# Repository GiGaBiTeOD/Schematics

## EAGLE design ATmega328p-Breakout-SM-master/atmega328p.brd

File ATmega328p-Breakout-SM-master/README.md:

# ATmega328p Breakout Board (Surface Mount version)
Eagle board and schematic files for a breakout of the popular ATmega328p microcontroller.

Currently available on Tindie: https://www.tindie.com/products/mwhelectronics/atmega328p-breakout-board/

## License Information
<br />This work is licensed under a <a rel="license" href="http://creativecommons.org/licenses/by-sa/4.0/">Creative Commons Attribution-ShareAlike 4.0 International License</a>.

Distributed as-is; no warranty is given.

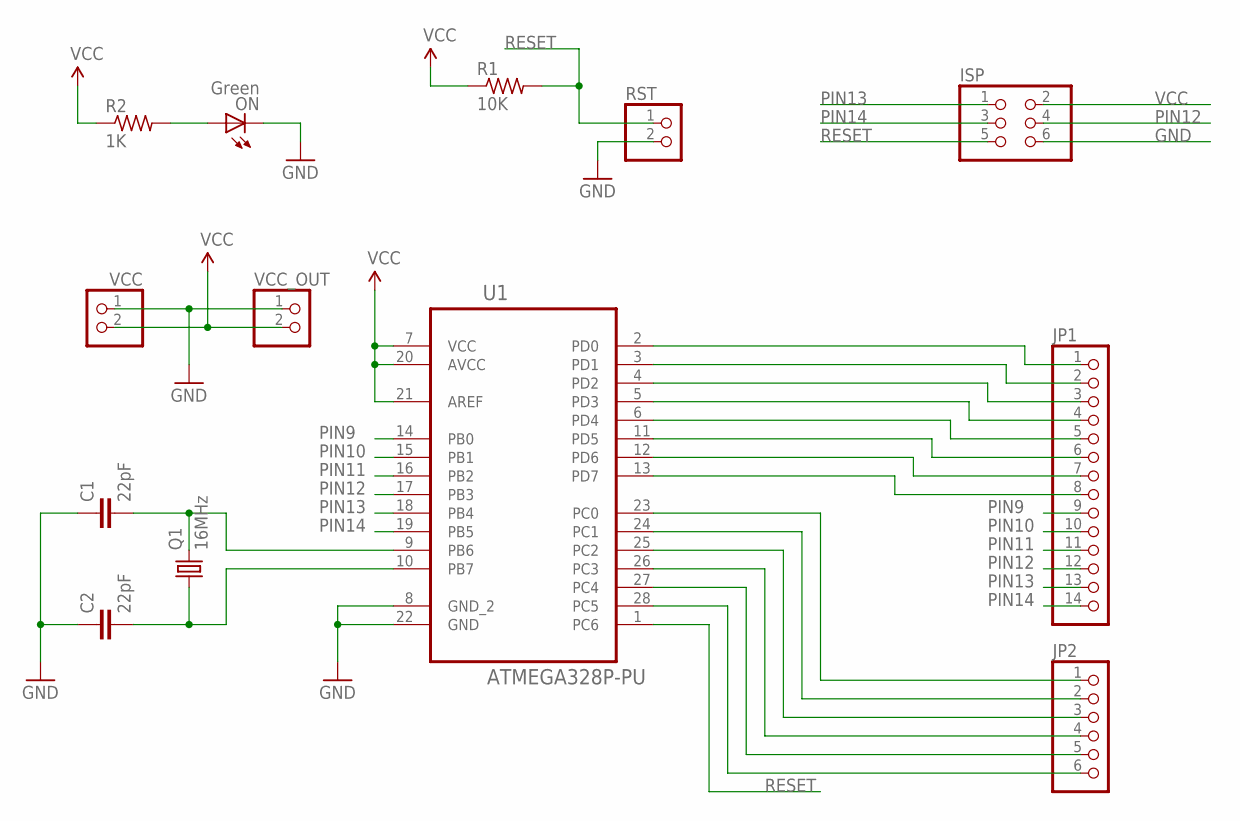
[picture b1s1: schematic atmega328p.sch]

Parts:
C1, C2: 22pF; C0603
ISP: PINHD-2X3; 2X03
JP1: PINHD-1X14; 1X14
JP2: PINHD-1X6; 1X06
ON: Green; CHIPLED_0805
Q1: 16MHz; HC49/S
R1: 10K; R0805
R2: 1K; R0805
RST: PINHD-1X2; 1X02
U1: ATMEGA328P-PU; DIP254P762X457-28
VCC: PINHD-1X2; 1X02
VCC_OUT: PINHD-1X2; 1X02

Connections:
GND: C1.1, C2.1, ISP.6, ON.C, RST.2, U1.8 (GND_2), U1.22 (GND), VCC.1, VCC_OUT.1
unnamed: C1.2, Q1.2, U1.9 (PB6)
unnamed: C2.2, Q1.1, U1.10 (PB7)
unnamed: ON.A, R2.2
unnamed: JP1.1, U1.2 (PD0)
unnamed: JP1.2, U1.3 (PD1)
unnamed: JP1.3, U1.4 (PD2)
unnamed: JP1.4, U1.5 (PD3)
unnamed: JP1.5, U1.6 (PD4)
unnamed: JP1.6, U1.11 (PD5)
unnamed: JP1.7, U1.12 (PD6)
unnamed: JP1.8, U1.13 (PD7)
unnamed: JP2.1, U1.23 (PC0)
unnamed: JP2.2, U1.24 (PC1)
unnamed: JP2.3, U1.25 (PC2)
unnamed: JP2.4, U1.26 (PC3)
unnamed: JP2.5, U1.27 (PC4)
unnamed: JP2.6, U1.28 (PC5)
PIN9: JP1.9, U1.14 (PB0)
PIN10: JP1.10, U1.15 (PB1)
PIN11: JP1.11, U1.16 (PB2)
PIN12: ISP.4, JP1.12, U1.17 (PB3)
PIN13: ISP.1, JP1.13, U1.18 (PB4)
PIN14: ISP.3, JP1.14, U1.19 (PB5)
RESET: ISP.5, R1.2, RST.1, U1.1 (PC6)
VCC: ISP.2, R1.1, R2.1, U1.7 (VCC), U1.20 (AVCC), U1.21 (AREF), VCC.2, VCC_OUT.2

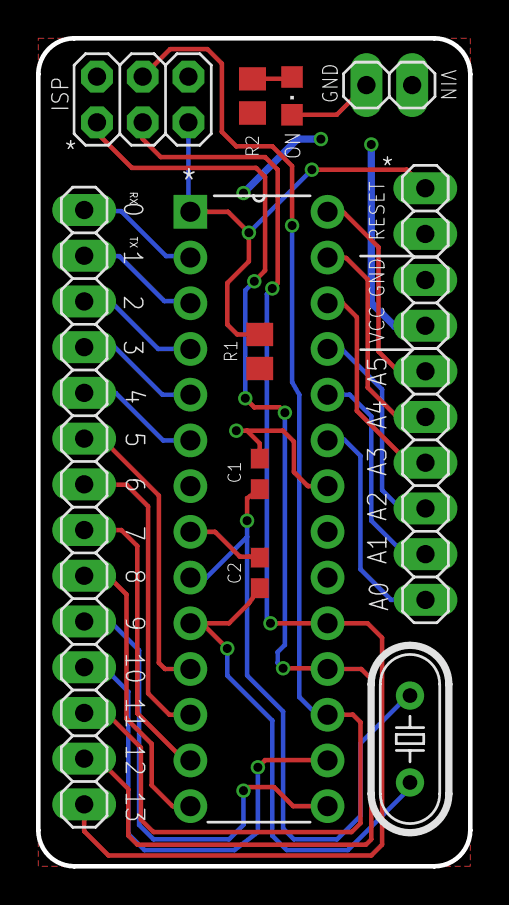
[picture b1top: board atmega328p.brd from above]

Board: 2 copper layers, 24.0 x 46.0 mm, 13 parts (0 on the bottom side), 26 nets.

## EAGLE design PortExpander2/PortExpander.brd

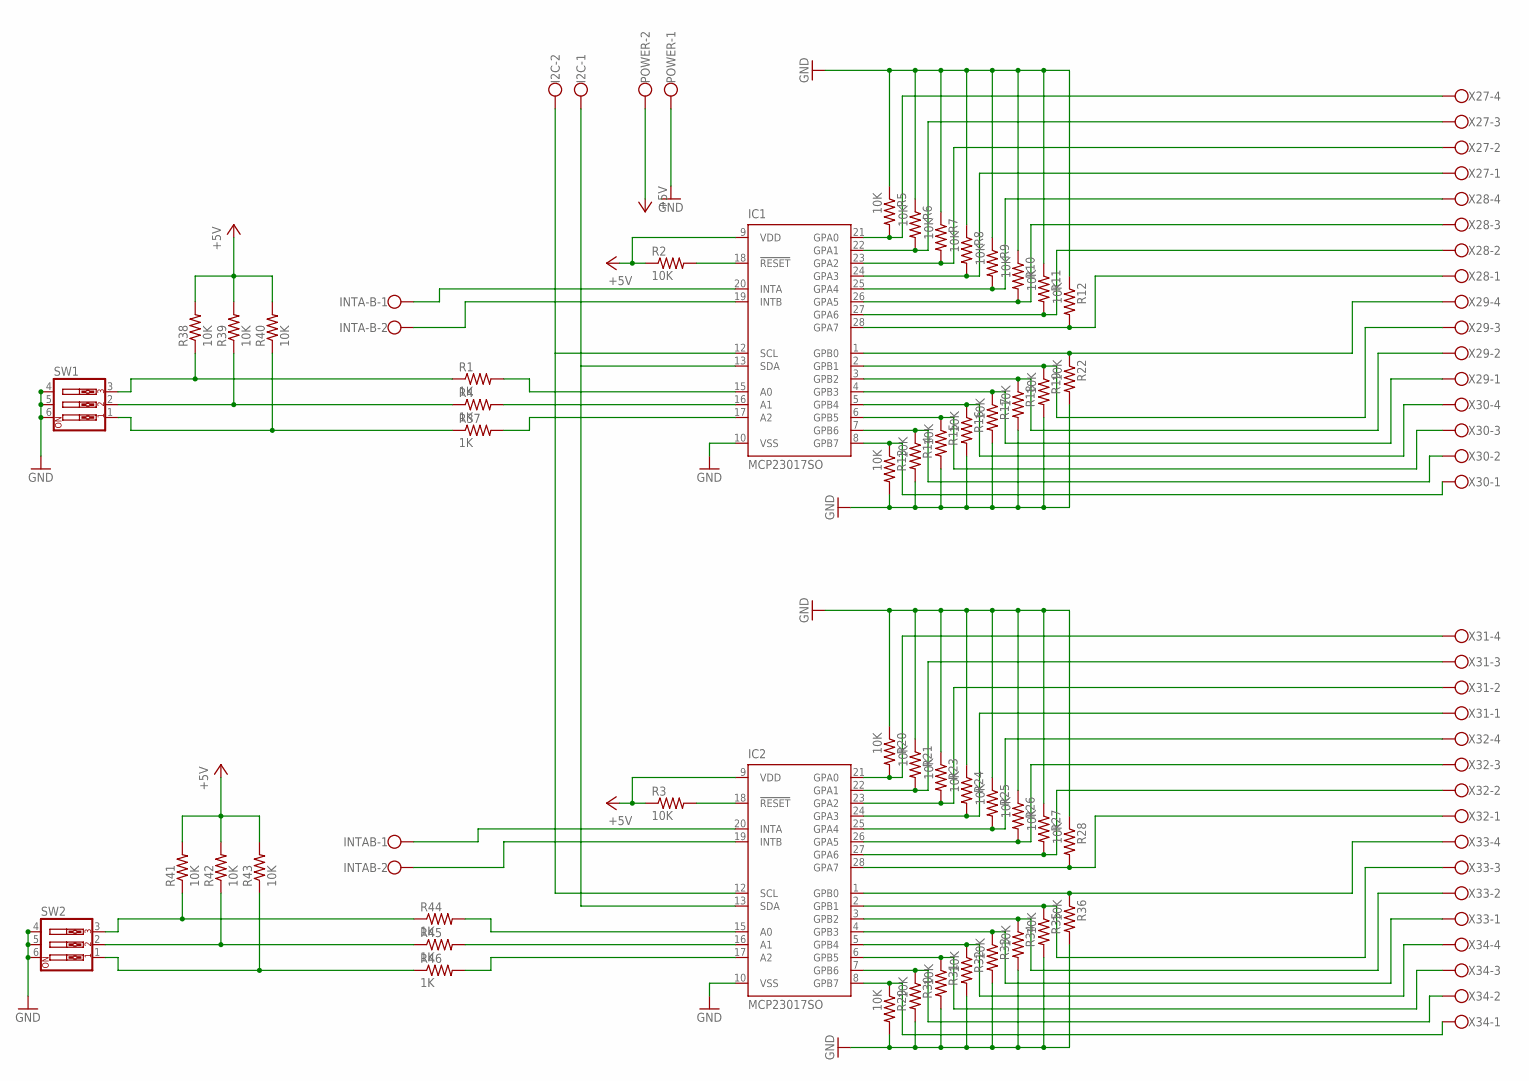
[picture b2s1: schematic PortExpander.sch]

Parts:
I2C: W237-102
IC1, IC2: MCP23017SO; SO28W
INTA-B: W237-102
INTAB: W237-102
POWER: W237-102
R1, R4, R37, R44, R45, R46: 1K; 1206
R2, R3, R5, R6, R7, R8, R9, R10, R11, R12, R13, R14, R15, R16, R17, R18, R19, R20, R21, R22, R23, R24, R25, R26, R27, R28, R29, R30, R31, R32, R33, R34, R35, R36, R38, R39, R40, R41, R42, R43: 10K; 1206
SW1, SW2: SW_DIP-3; EDG-03
X27, X28, X29, X30, X31, X32, X33, X34: W237-4

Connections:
+5V: IC1.9 (VDD), IC2.9 (VDD), POWER.2, R2.1, R3.1, R38.2, R39.2, R40.2, R41.2, R42.2, R43.2
GND: IC1.10 (VSS), IC2.10 (VSS), POWER.1, R5.1, R6.1, R7.1, R8.1, R9.1, R10.1, R11.1, R12.1, R13.2, R14.2, R15.2, R16.2, R17.2, R18.2, R19.2, R20.1, R21.1, R22.2, R23.1, R24.1, R25.1, R26.1, R27.1, R28.1, R29.2, R30.2, R31.2, R32.2, R33.2, R34.2, R35.2, R36.2, SW1.4, SW1.5, SW1.6, SW2.4, SW2.5, SW2.6
GPA0: IC1.21 (GPA0), R5.2, X27.4
GPA0-2: IC2.21 (GPA0), R20.2, X31.4
GPA1: IC1.22 (GPA1), R6.2, X27.3
GPA1-2: IC2.22 (GPA1), R21.2, X31.3
GPA2: IC1.23 (GPA2), R7.2, X27.2
GPA2-2: IC2.23 (GPA2), R23.2, X31.2
GPA3: IC1.24 (GPA3), R8.2, X27.1
GPA3-2: IC2.24 (GPA3), R24.2, X31.1
GPA4: IC1.25 (GPA4), R9.2, X28.4
GPA4-2: IC2.25 (GPA4), R25.2, X32.4
GPA5: IC1.26 (GPA5), R10.2, X28.3
GPA5-2: IC2.26 (GPA5), R26.2, X32.3
GPA6: IC1.27 (GPA6), R11.2, X28.2
GPA6-2: IC2.27 (GPA6), R27.2, X32.2
GPA7: IC1.28 (GPA7), R12.2, X28.1
GPA7-2: IC2.28 (GPA7), R28.2, X32.1
GPB0: IC1.1 (GPB0), R22.1, X29.4
GPB0-2: IC2.1 (GPB0), R36.1, X33.4
GPB1: IC1.2 (GPB1), R19.1, X29.3
GPB1-2: IC2.2 (GPB1), R35.1, X33.3
GPB2: IC1.3 (GPB2), R18.1, X29.2
GPB2-2: IC2.3 (GPB2), R34.1, X33.2
GPB3: IC1.4 (GPB3), R17.1, X29.1
GPB3-2: IC2.4 (GPB3), R33.1, X33.1
GPB4: IC1.5 (GPB4), R16.1, X30.4
GPB4-2: IC2.5 (GPB4), R32.1, X34.4
GPB5: IC1.6 (GPB5), R15.1, X30.3
GPB5-2: IC2.6 (GPB5), R31.1, X34.3
GPB6: IC1.7 (GPB6), R14.1, X30.2
GPB6-2: IC2.7 (GPB6), R30.1, X34.2
GPB7: IC1.8 (GPB7), R13.1, X30.1
GPB7-2: IC2.8 (GPB7), R29.1, X34.1
INTA: IC1.20 (INTA), INTA-B.1
INTA2: IC2.20 (INTA), INTAB.1
INTB: IC1.19 (INTB), INTA-B.2
INTB2: IC2.19 (INTB), INTAB.2
unnamed: IC2.15 (A0), R44.2
unnamed: IC1.15 (A0), R1.2
unnamed: IC1.16 (A1), R4.2
unnamed: IC1.17 (A2), R37.2
unnamed: R1.1, R38.1, SW1.3
unnamed: R4.1, R39.1, SW1.2
unnamed: R37.1, R40.1, SW1.1
unnamed: R41.1, R44.1, SW2.3
unnamed: IC2.16 (A1), R45.2
unnamed: R43.1, R46.1, SW2.1
unnamed: R42.1, R45.1, SW2.2
unnamed: IC2.17 (A2), R46.2
RESET: IC1.18 (!RESET), R2.2
RESET-2: IC2.18 (!RESET), R3.2
SCL: I2C.1, IC1.13 (SDA), IC2.13 (SDA)
SDA: I2C.2, IC1.12 (SCL), IC2.12 (SCL)

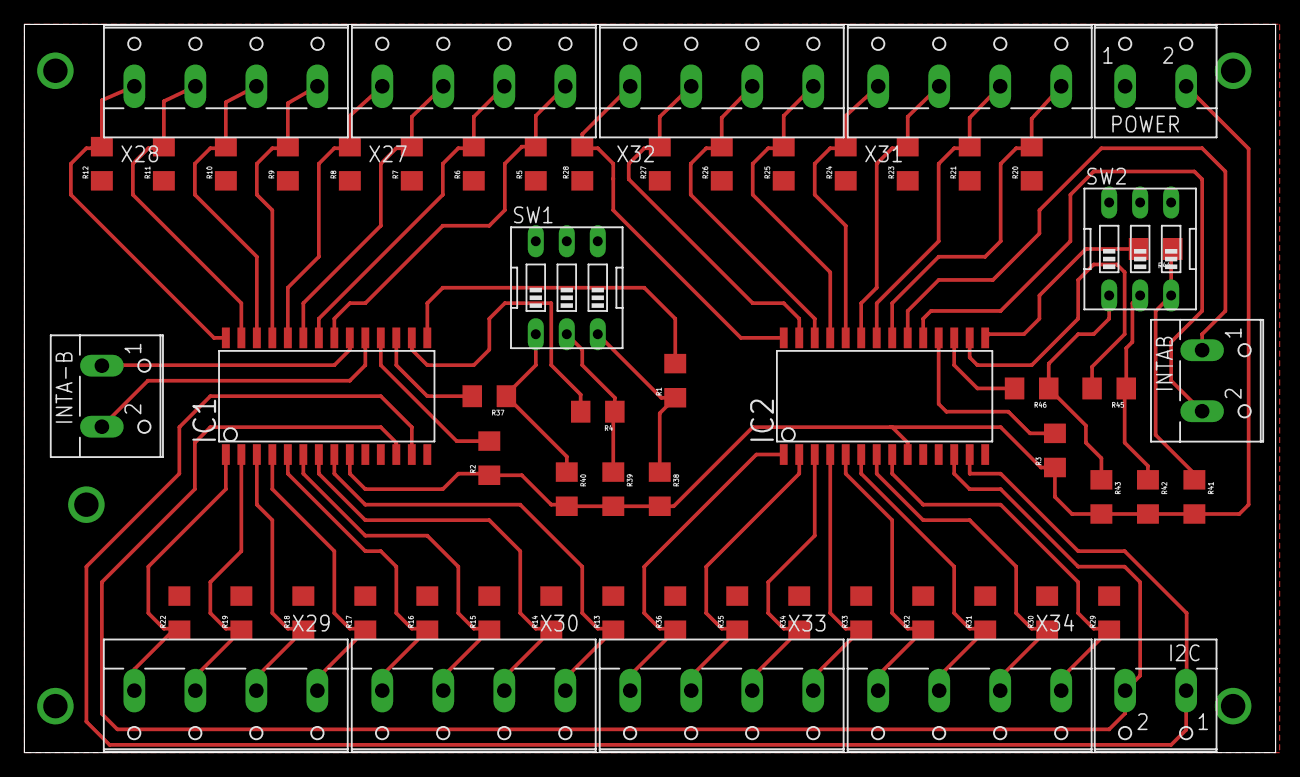
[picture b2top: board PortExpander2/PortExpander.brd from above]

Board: 2 copper layers, 102.5 x 59.7 mm, 62 parts (0 on the bottom side), 54 nets.

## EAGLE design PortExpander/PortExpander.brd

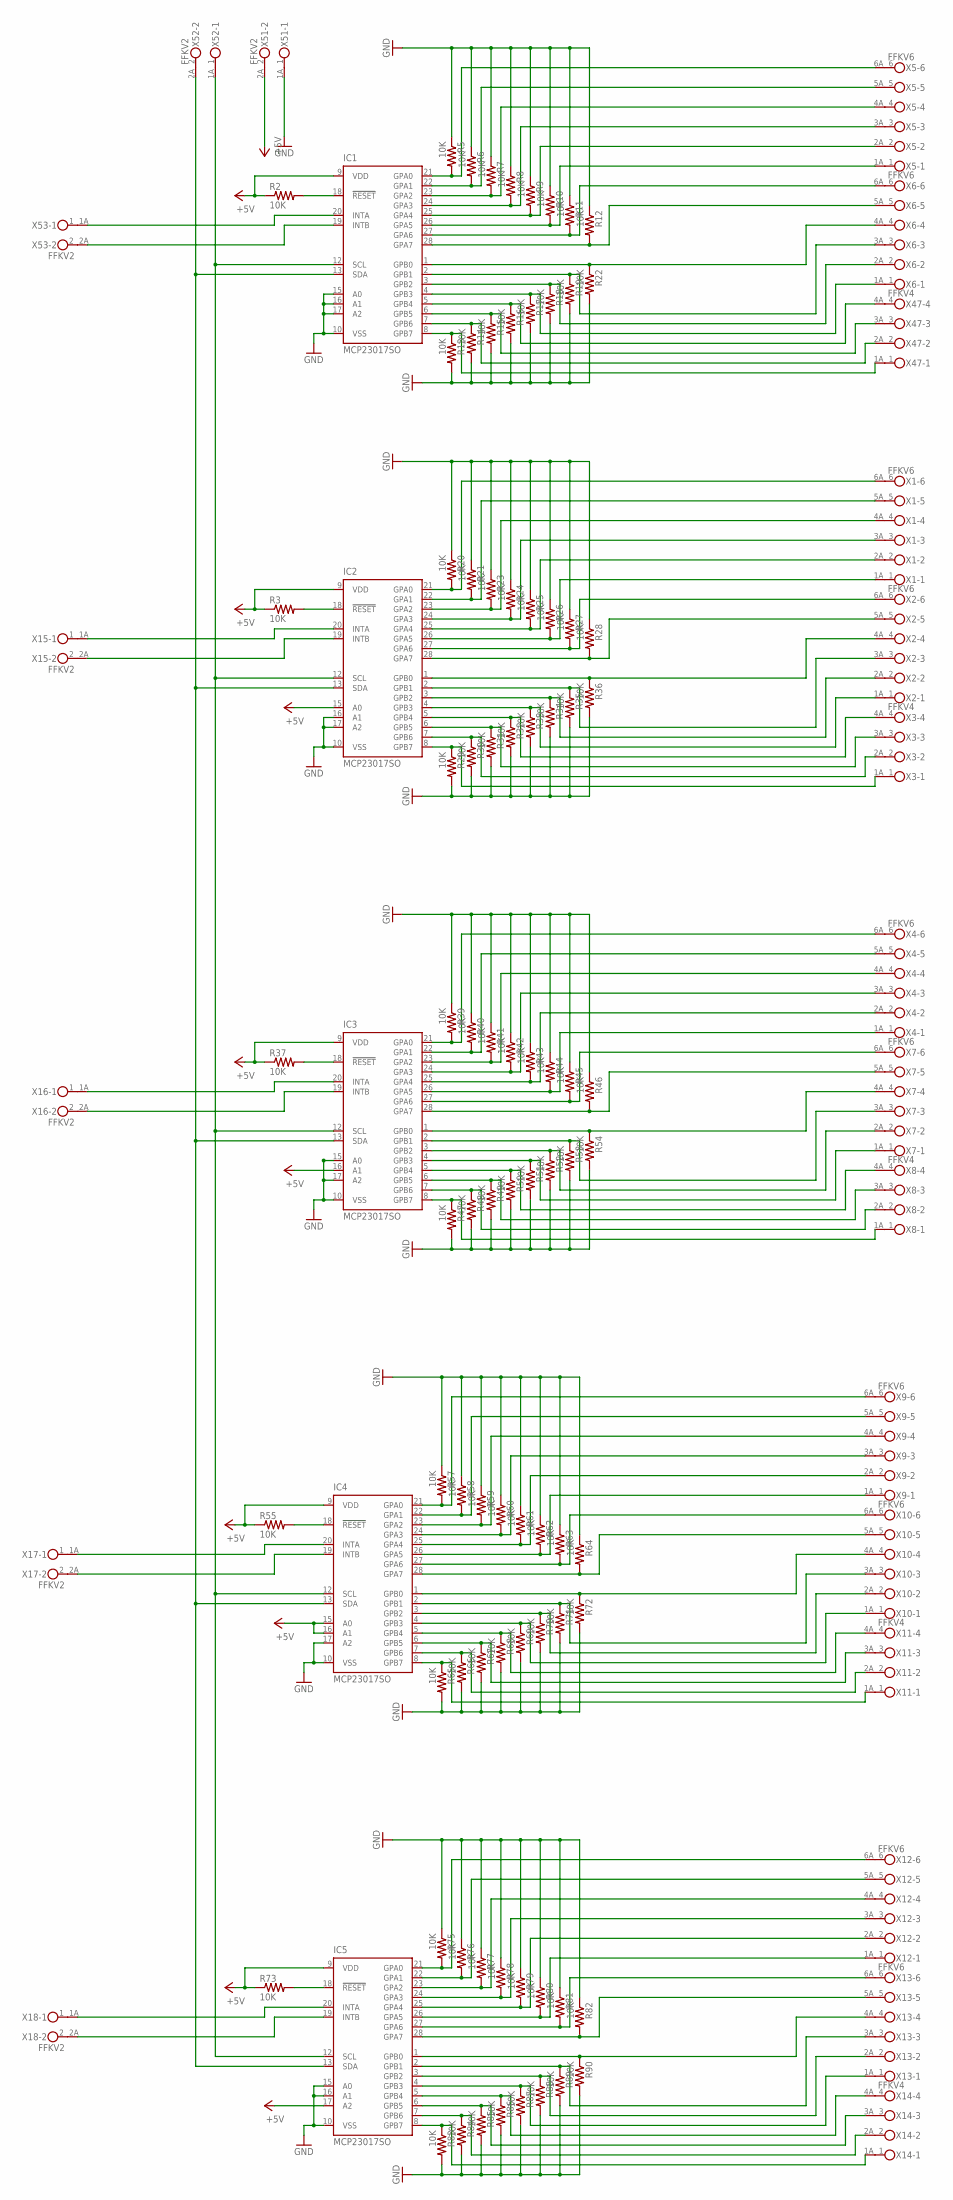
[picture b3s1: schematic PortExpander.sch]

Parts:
IC1, IC2, IC3, IC4, IC5: MCP23017SO; SO28W
R2, R3, R5, R6, R7, R8, R9, R10, R11, R12, R13, R14, R15, R16, R17, R18, R19, R20, R21, R22, R23, R24, R25, R26, R27, R28, R29, R30, R31, R32, R33, R34, R35, R36, R37, R39, R40, R41, R42, R43, R44, R45, R46, R47, R48, R49, R50, R51, R52, R53, R54, R55, R57, R58, R59, R60, R61, R62, R63, R64, R65, R66, R67, R68, R69, R70, R71, R72, R73, R75, R76, R77, R78, R79, R80, R81, R82, R83, R84, R85, R86, R87, R88, R89, R90: 10K; 1206
X1, X2, X4, X5, X6, X7, X9, X10, X12, X13: FFKV6
X3, X8, X11, X14, X47: FFKV4
X15, X16, X17, X18, X51, X52, X53: FFKV2

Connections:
+5V: IC1.9 (VDD), IC2.9 (VDD), IC2.15 (A0), IC3.9 (VDD), IC3.16 (A1), IC4.9 (VDD), IC4.15 (A0), IC4.16 (A1), IC5.9 (VDD), IC5.17 (A2), R2.1, R3.1, R37.1, R55.1, R73.1, X51.2A (2)
GND: IC1.10 (VSS), IC1.15 (A0), IC1.16 (A1), IC1.17 (A2), IC2.10 (VSS), IC2.16 (A1), IC2.17 (A2), IC3.10 (VSS), IC3.15 (A0), IC3.17 (A2), IC4.10 (VSS), IC4.17 (A2), IC5.10 (VSS), IC5.15 (A0), IC5.16 (A1), R5.1, R6.1, R7.1, R8.1, R9.1, R10.1, R11.1, R12.1, R13.2, R14.2, R15.2, R16.2, R17.2, R18.2, R19.2, R20.1, R21.1, R22.2, R23.1, R24.1, R25.1, R26.1, R27.1, R28.1, R29.2, R30.2, R31.2, R32.2, R33.2, R34.2, R35.2, R36.2, R39.1, R40.1, R41.1, R42.1, R43.1, R44.1, R45.1, R46.1, R47.2, R48.2, R49.2, R50.2, R51.2, R52.2, R53.2, R54.2, R57.1, R58.1, R59.1, R60.1, R61.1, R62.1, R63.1, R64.1, R65.2, R66.2, R67.2, R68.2, R69.2, R70.2, R71.2, R72.2, R75.1, R76.1, R77.1, R78.1, R79.1, R80.1, R81.1, R82.1, R83.2, R84.2, R85.2, R86.2, R87.2, R88.2, R89.2, R90.2, X51.1A (2)
unnamed: IC1.18 (!RESET), R2.2
unnamed: IC2.18 (!RESET), R3.2
unnamed: IC1.21 (GPA0), R5.2, X5.6A (2)
unnamed: IC1.22 (GPA1), R6.2, X5.5A (2)
unnamed: IC1.23 (GPA2), R7.2, X5.4A (2)
unnamed: IC1.24 (GPA3), R8.2, X5.3A (2)
unnamed: IC1.25 (GPA4), R9.2, X5.2A (2)
unnamed: IC1.26 (GPA5), R10.2, X5.1A (2)
unnamed: IC1.27 (GPA6), R11.2, X6.6A (2)
unnamed: IC1.28 (GPA7), R12.2, X6.5A (2)
unnamed: IC2.20 (INTA), X15.1A (2)
unnamed: IC1.8 (GPB7), R13.1, X47.1A (2)
unnamed: IC1.7 (GPB6), R14.1, X47.2A (2)
unnamed: IC1.6 (GPB5), R15.1, X47.3A (2)
unnamed: IC1.5 (GPB4), R16.1, X47.4A (2)
unnamed: IC1.4 (GPB3), R17.1, X6.1A (2)
unnamed: IC1.3 (GPB2), R18.1, X6.2A (2)
unnamed: IC1.2 (GPB1), R19.1, X6.3A (2)
unnamed: IC1.1 (GPB0), R22.1, X6.4A (2)
unnamed: IC2.19 (INTB), X15.2A (2)
unnamed: IC2.21 (GPA0), R20.2, X1.6A (2)
unnamed: IC2.22 (GPA1), R21.2, X1.5A (2)
unnamed: IC2.23 (GPA2), R23.2, X1.4A (2)
unnamed: IC2.24 (GPA3), R24.2, X1.3A (2)
unnamed: IC2.25 (GPA4), R25.2, X1.2A (2)
unnamed: IC2.26 (GPA5), R26.2, X1.1A (2)
unnamed: IC2.27 (GPA6), R27.2, X2.6A (2)
unnamed: IC2.28 (GPA7), R28.2, X2.5A (2)
unnamed: IC2.8 (GPB7), R29.1, X3.1A (2)
unnamed: IC2.7 (GPB6), R30.1, X3.2A (2)
unnamed: IC2.6 (GPB5), R31.1, X3.3A (2)
unnamed: IC2.5 (GPB4), R32.1, X3.4A (2)
unnamed: IC2.4 (GPB3), R33.1, X2.1A (2)
unnamed: IC2.3 (GPB2), R34.1, X2.2A (2)
unnamed: IC2.2 (GPB1), R35.1, X2.3A (2)
unnamed: IC2.1 (GPB0), R36.1, X2.4A (2)
unnamed: IC3.18 (!RESET), R37.2
unnamed: IC3.20 (INTA), X16.1A (2)
unnamed: IC3.19 (INTB), X16.2A (2)
unnamed: IC3.21 (GPA0), R39.2, X4.6A (2)
unnamed: IC3.22 (GPA1), R40.2, X4.5A (2)
unnamed: IC3.23 (GPA2), R41.2, X4.4A (2)
unnamed: IC3.24 (GPA3), R42.2, X4.3A (2)
unnamed: IC3.25 (GPA4), R43.2, X4.2A (2)
unnamed: IC3.26 (GPA5), R44.2, X4.1A (2)
unnamed: IC3.27 (GPA6), R45.2, X7.6A (2)
unnamed: IC3.28 (GPA7), R46.2, X7.5A (2)
unnamed: IC3.8 (GPB7), R47.1, X8.1A (2)
unnamed: IC3.7 (GPB6), R48.1, X8.2A (2)
unnamed: IC3.6 (GPB5), R49.1, X8.3A (2)
unnamed: IC3.5 (GPB4), R50.1, X8.4A (2)
unnamed: IC3.4 (GPB3), R51.1, X7.1A (2)
unnamed: IC3.3 (GPB2), R52.1, X7.2A (2)
unnamed: IC3.2 (GPB1), R53.1, X7.3A (2)
unnamed: IC3.1 (GPB0), R54.1, X7.4A (2)
unnamed: IC4.18 (!RESET), R55.2
unnamed: IC4.20 (INTA), X17.1A (2)
unnamed: IC4.19 (INTB), X17.2A (2)
unnamed: IC4.21 (GPA0), R57.2, X9.6A (2)
unnamed: IC4.22 (GPA1), R58.2, X9.5A (2)
unnamed: IC4.23 (GPA2), R59.2, X9.4A (2)
unnamed: IC4.24 (GPA3), R60.2, X9.3A (2)
unnamed: IC1.20 (INTA), X53.1A (2)
unnamed: IC1.19 (INTB), X53.2A (2)
unnamed: IC4.25 (GPA4), R61.2, X9.2A (2)
unnamed: IC4.26 (GPA5), R62.2, X9.1A (2)
unnamed: IC4.27 (GPA6), R63.2, X10.6A (2)
unnamed: IC4.28 (GPA7), R64.2, X10.5A (2)
unnamed: IC4.8 (GPB7), R65.1, X11.1A (2)
unnamed: IC4.7 (GPB6), R66.1, X11.2A (2)
unnamed: IC4.6 (GPB5), R67.1, X11.3A (2)
unnamed: IC4.5 (GPB4), R68.1, X11.4A (2)
unnamed: IC4.4 (GPB3), R69.1, X10.1A (2)
unnamed: IC4.3 (GPB2), R70.1, X10.2A (2)
unnamed: IC4.2 (GPB1), R71.1, X10.3A (2)
unnamed: IC4.1 (GPB0), R72.1, X10.4A (2)
unnamed: IC5.18 (!RESET), R73.2
unnamed: IC5.20 (INTA), X18.1A (2)
unnamed: IC5.19 (INTB), X18.2A (2)
unnamed: IC5.21 (GPA0), R75.2, X12.6A (2)
unnamed: IC5.22 (GPA1), R76.2, X12.5A (2)
unnamed: IC5.23 (GPA2), R77.2, X12.4A (2)
unnamed: IC5.24 (GPA3), R78.2, X12.3A (2)
unnamed: IC5.25 (GPA4), R79.2, X12.2A (2)
unnamed: IC5.26 (GPA5), R80.2, X12.1A (2)
unnamed: IC5.27 (GPA6), R81.2, X13.6A (2)
unnamed: IC5.28 (GPA7), R82.2, X13.5A (2)
unnamed: IC5.8 (GPB7), R83.1, X14.1A (2)
unnamed: IC5.7 (GPB6), R84.1, X14.2A (2)
unnamed: IC5.6 (GPB5), R85.1, X14.3A (2)
unnamed: IC5.5 (GPB4), R86.1, X14.4A (2)
unnamed: IC5.4 (GPB3), R87.1, X13.1A (2)
unnamed: IC5.3 (GPB2), R88.1, X13.2A (2)
unnamed: IC5.2 (GPB1), R89.1, X13.3A (2)
unnamed: IC5.1 (GPB0), R90.1, X13.4A (2)
SCL: IC1.12 (SCL), IC2.12 (SCL), IC3.12 (SCL), IC4.12 (SCL), IC5.12 (SCL), X52.1A (2)
SDA: IC1.13 (SDA), IC2.13 (SDA), IC3.13 (SDA), IC4.13 (SDA), IC5.13 (SDA), X52.2A (2)

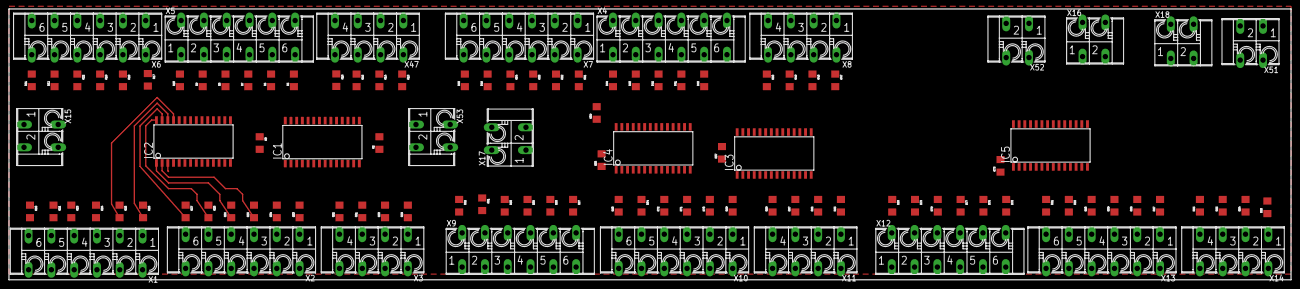
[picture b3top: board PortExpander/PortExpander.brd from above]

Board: 2 copper layers, 285.7 x 60.4 mm, 112 parts (0 on the bottom side), 99 nets.

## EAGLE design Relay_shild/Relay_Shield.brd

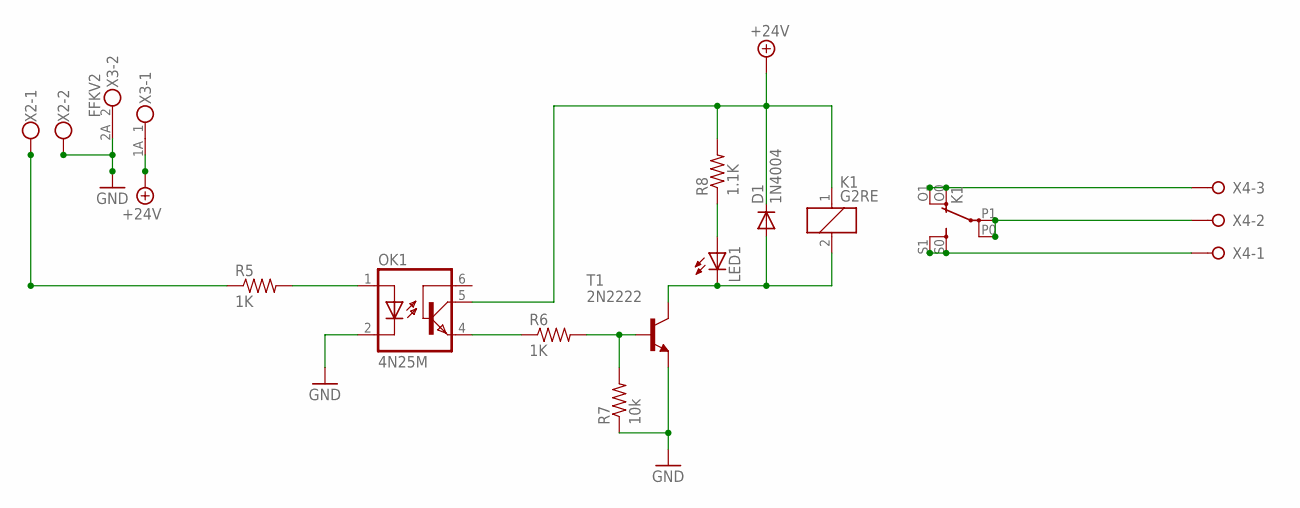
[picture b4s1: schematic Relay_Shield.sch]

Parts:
D1: 1N4004; DO41-10
K1: G2RE
LED1: LED3MM
OK1: 4N25M; DIL06
R5, R6: 1K; 1206
R7: 10k; 1206
R8: 1.1K; 1206
T1: 2N2222; TO18
X2: W237-102
X3: FFKV2
X4: W237-3E

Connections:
+24V: D1.C, K1.1, OK1.5 (COL), R8.2, X3.1A (2)
GND: OK1.2 (C), R7.1, T1.1 (E), X2.2, X3.2A (2)
unnamed: OK1.1 (A), R5.2
unnamed: OK1.4 (EMI), R6.1
unnamed: R6.2, R7.2, T1.2 (B)
unnamed: R5.1, X2.1
unnamed: D1.A, K1.2, LED1.K (C), T1.3 (C)
unnamed: LED1.A, R8.1
unnamed: K1.P0, K1.P1, X4.2
unnamed: K1.O0 (O), K1.O1 (O), X4.3
unnamed: K1.S0 (S), K1.S1 (S), X4.1

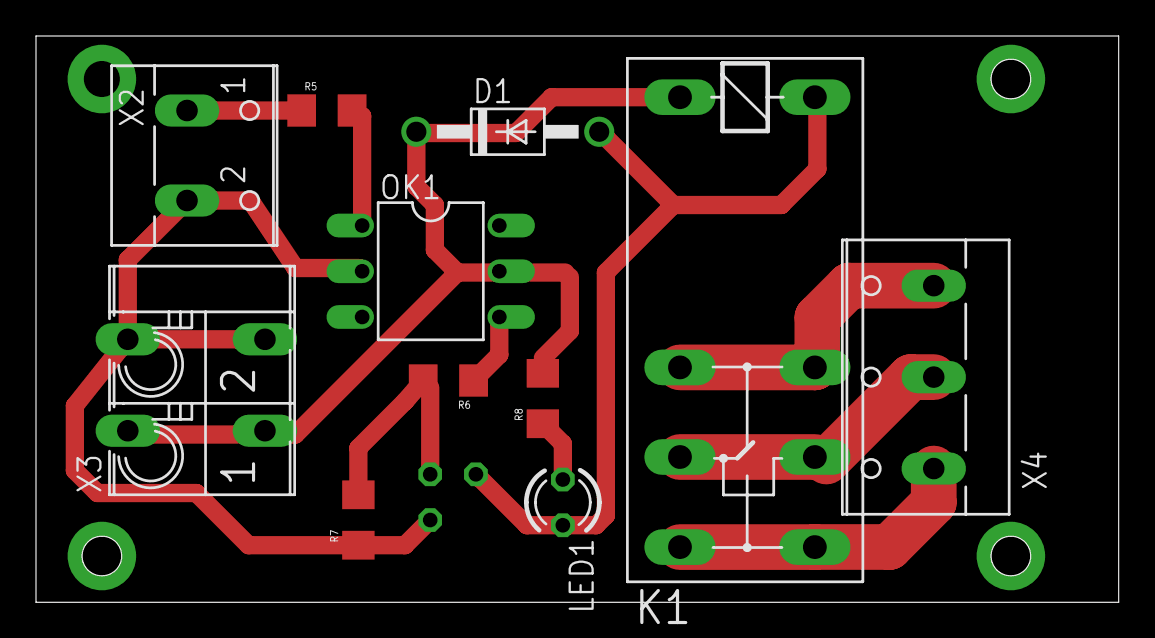
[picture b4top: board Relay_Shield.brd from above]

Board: 2 copper layers, 60.1 x 31.5 mm, 12 parts (1 on the bottom side), 11 nets.

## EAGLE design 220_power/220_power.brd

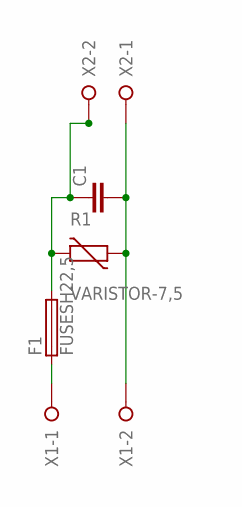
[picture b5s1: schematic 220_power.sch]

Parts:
C1: C15/8; C15B8
F1: FUSESH22,5; SH22,5
R1: VARISTOR-7,5; R-7,5
X1, X2: W237-02P; W237-132

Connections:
unnamed: F1.1, X1.1
unnamed: C1.1, F1.2, R1.2, X2.2
unnamed: C1.2, R1.1, X1.2, X2.1

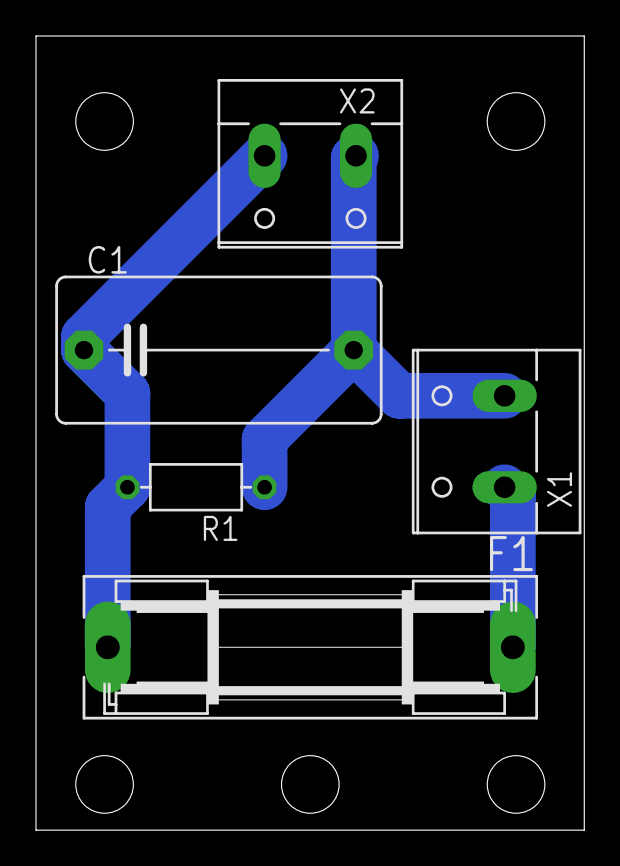
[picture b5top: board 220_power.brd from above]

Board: 2 copper layers, 30.5 x 44.1 mm, 5 parts (0 on the bottom side), 3 nets.

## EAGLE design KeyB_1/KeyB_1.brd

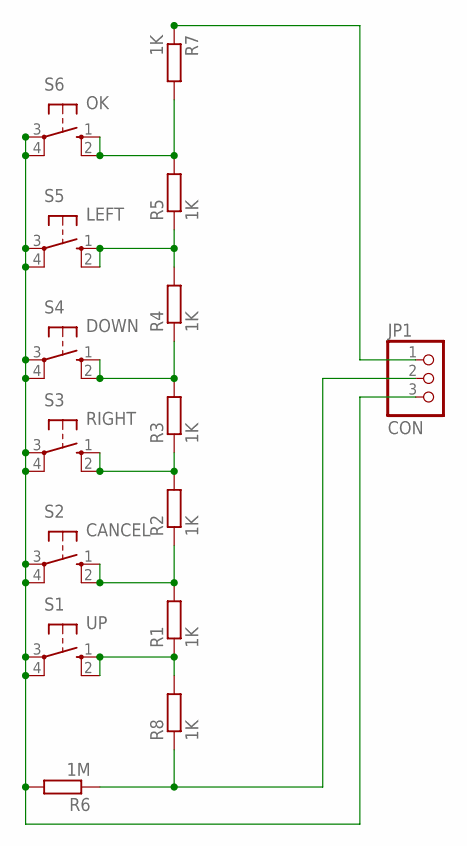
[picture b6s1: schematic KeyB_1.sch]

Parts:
JP1: CON; 1X03
R1, R2, R3, R4, R5, R7, R8: 1K; R1206W
R6: 1M; R1206W
S1: UP; B3F-10XX
S2: CANCEL; B3F-10XX
S3: RIGHT; B3F-10XX
S4: DOWN; B3F-10XX
S5: LEFT; B3F-10XX
S6: OK; B3F-10XX

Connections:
+5V: JP1.1, R7.1
AN_IN: JP1.3, R6.2, S1.3, S1.4 (P1), S2.3, S2.4 (P1), S3.3, S3.4 (P1), S4.3, S4.4 (P1), S5.3, S5.4 (P1), S6.3, S6.4 (P1)
GND: JP1.2, R6.1, R8.1
unnamed: R5.2, R7.2, S6.1 (S), S6.2 (S1)
unnamed: R4.2, R5.1, S5.1 (S), S5.2 (S1)
unnamed: R2.2, R3.1, S3.1 (S), S3.2 (S1)
unnamed: R3.2, R4.1, S4.1 (S), S4.2 (S1)
unnamed: R1.1, R8.2, S1.1 (S), S1.2 (S1)
unnamed: R1.2, R2.1, S2.1 (S), S2.2 (S1)

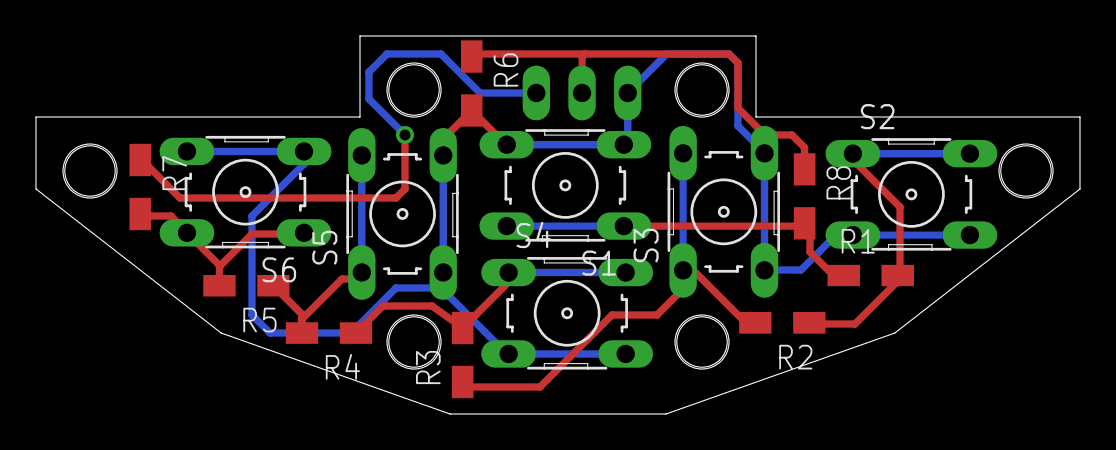
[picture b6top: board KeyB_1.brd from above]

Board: 2 copper layers, 58.0 x 21.0 mm, 15 parts (1 on the bottom side), 9 nets.

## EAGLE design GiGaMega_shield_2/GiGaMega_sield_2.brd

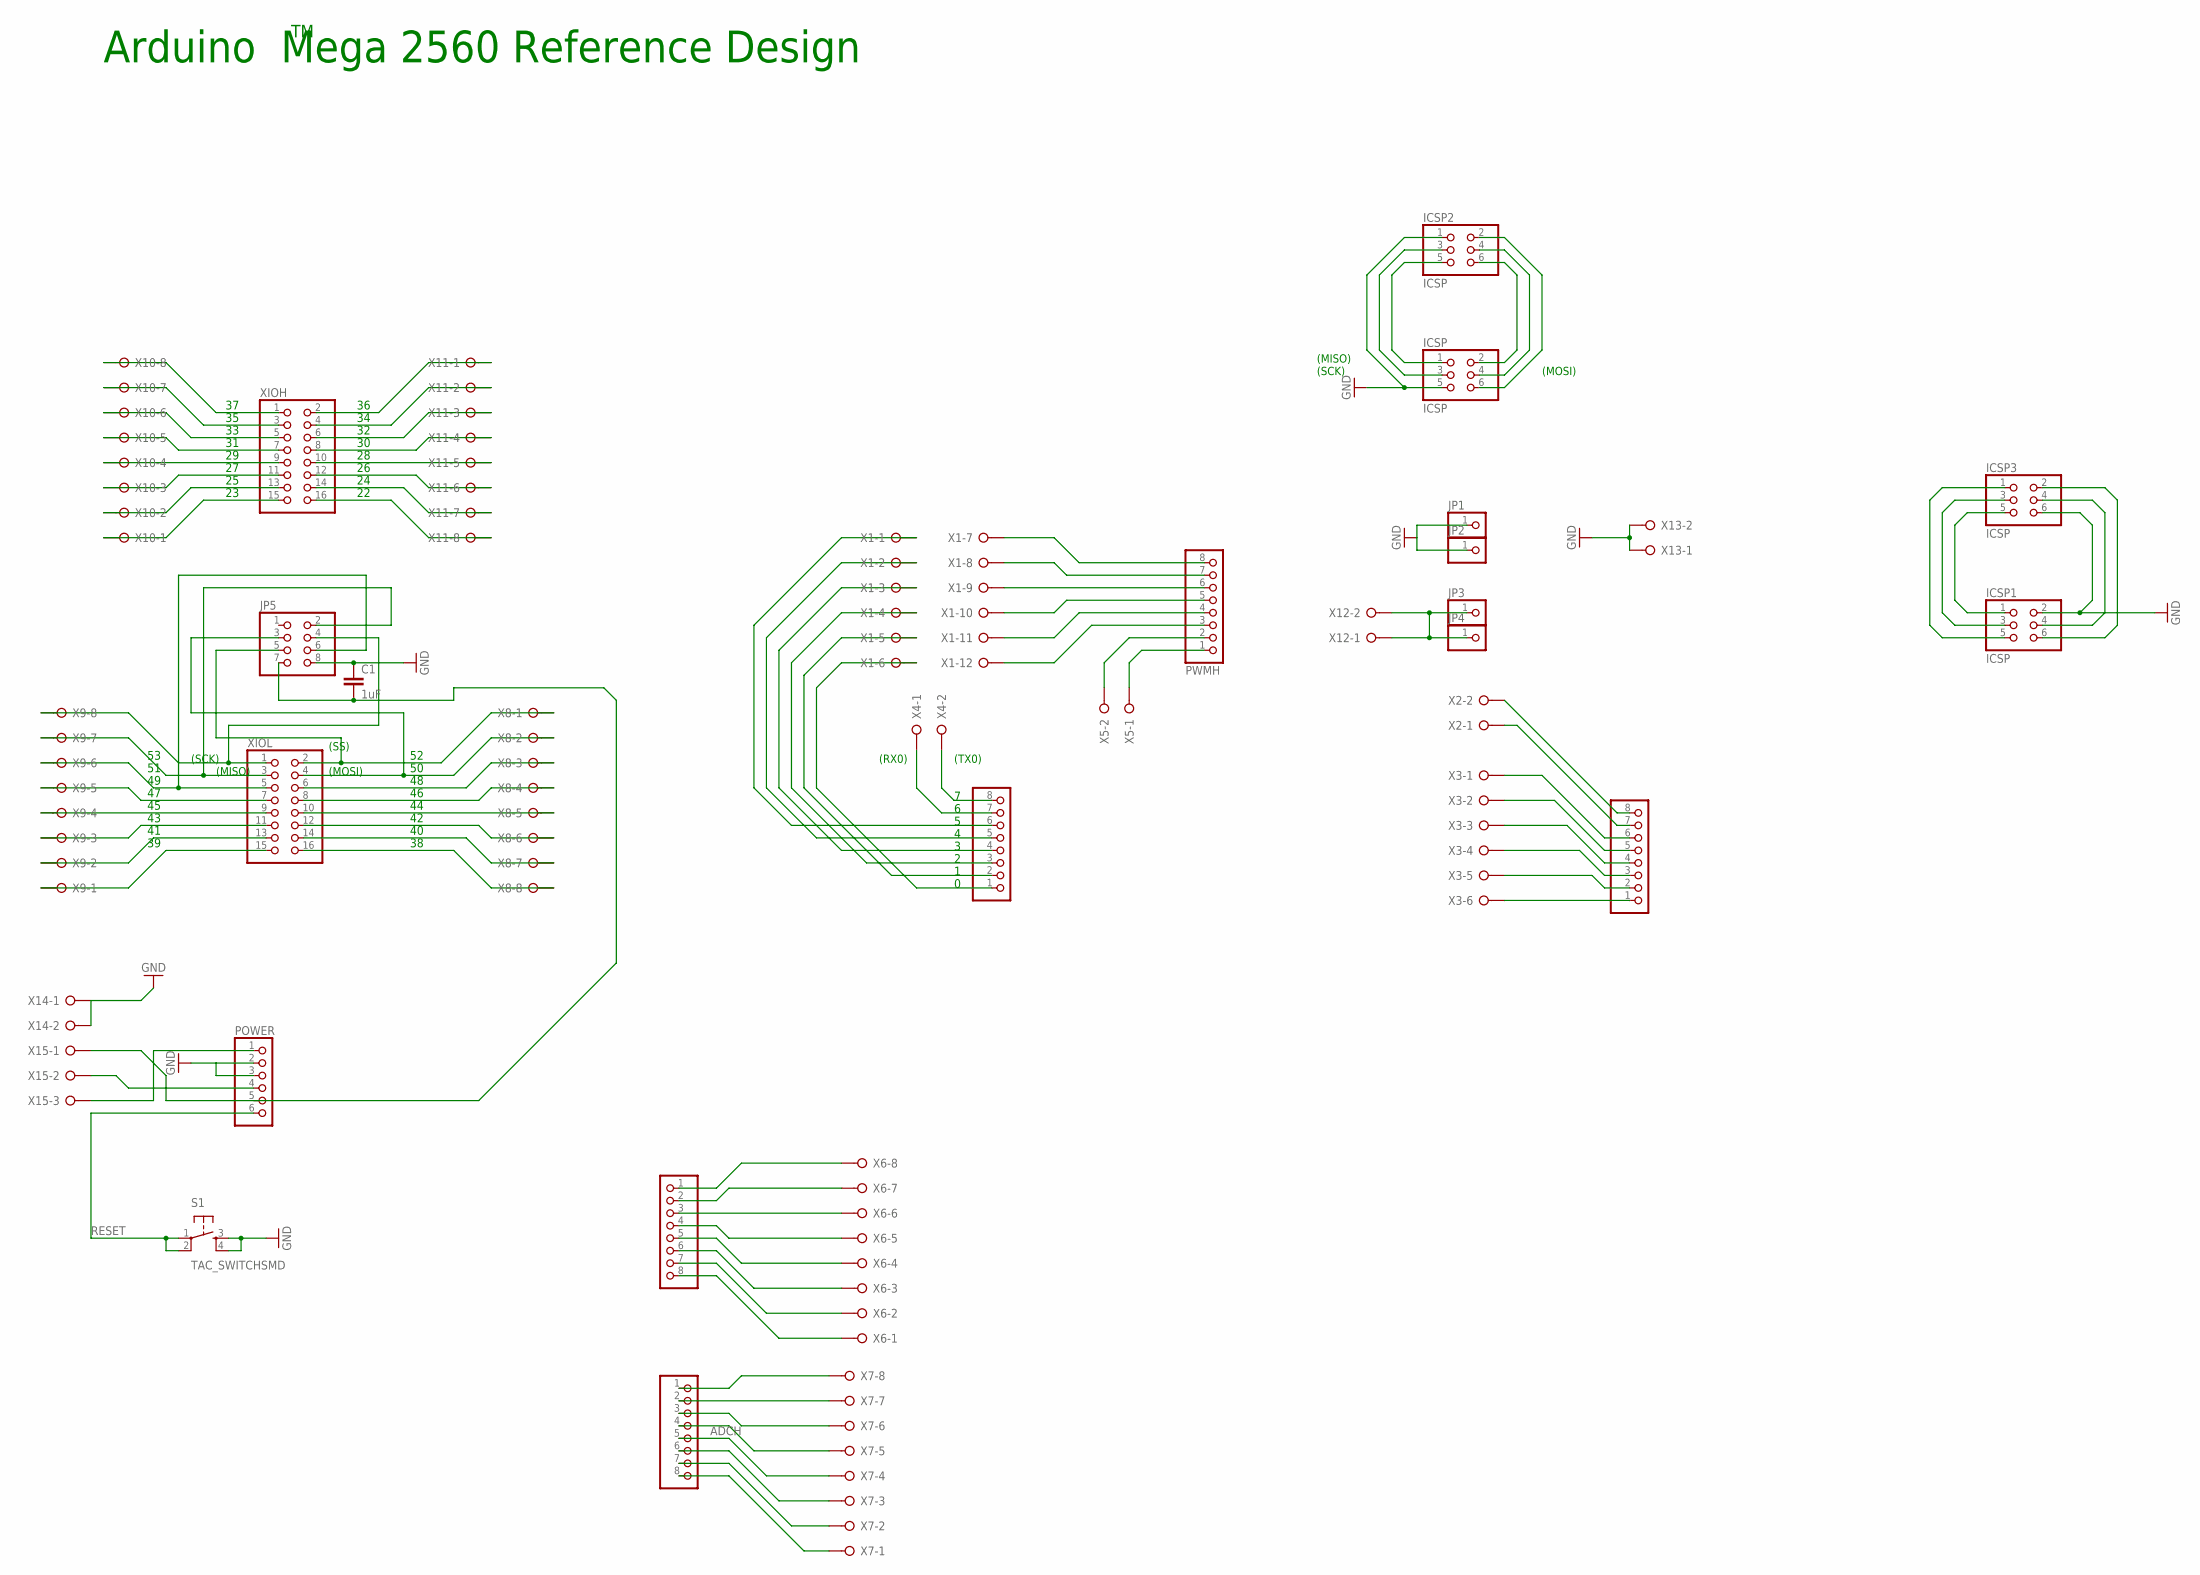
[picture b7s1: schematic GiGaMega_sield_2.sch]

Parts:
ADCH: PINHD-1X8; 1X08
ADCL: PINHD-1X8; 1X08
C1: 1uF; 1206
COMMUNICATION: PINHD-1X8; 1X08
ICSP, ICSP1, ICSP2, ICSP3: ICSP; 2X03
JP1, JP2, JP3, JP4: PINHD-1X1; 1X01
JP5: PINHD-2X4; 2X04
POWER: PINHD-1X6; 1X06
PWMH: PINHD-1X8; 1X08
PWML: PINHD-1X8; 1X08
S1: TAC_SWITCHSMD; TACTILE-SWITCH-SMD
X1: W237-12P
X2, X4, X5, X12, X13, X14: W237-02P; W237-132
X3: W237-06P; W237-6P
X6, X7, X8, X9, X10, X11: W237-08P; W237-8P
X15: W237-03P; W237-133
XIOH: PINHD-2X8; 2X08
XIOL: PINHD-2X8; 2X08

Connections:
CE: JP5.6, X9.6, XIOL.5
CSN: JP5.5, X8.1, XIOL.2
GND: C1.1, ICSP.5, ICSP1.2, ICSP2.1, ICSP3.6, JP1.1, JP2.1, JP5.8, POWER.2, POWER.3, S1.3, S1.4, X13.1, X13.2, X14.1, X14.2
MISO: JP5.2, X9.7, XIOL.3
MOSI: JP5.3, X8.2, XIOL.4
N: X8.3, XIOL.6
unnamed: ICSP1.1, ICSP3.5
unnamed: ICSP1.3, ICSP3.3
unnamed: PWMH.8, X1.7
unnamed: PWMH.7, X1.8
unnamed: PWMH.6, X1.9
unnamed: PWMH.5, X1.10
unnamed: PWMH.4, X1.11
unnamed: PWMH.3, X1.12
unnamed: PWML.1, X1.6
unnamed: PWML.2, X1.5
unnamed: PWML.3, X1.4
unnamed: PWML.4, X1.3
unnamed: PWML.5, X1.2
unnamed: PWML.6, X1.1
unnamed: ICSP.1, ICSP2.5
unnamed: ICSP.3, ICSP2.3
unnamed: ICSP1.5, ICSP3.1
unnamed: ICSP.2, ICSP2.6
unnamed: ICSP.4, ICSP2.4
unnamed: ICSP1.6, ICSP3.2
unnamed: ICSP.6, ICSP2.2
unnamed: ICSP1.4, ICSP3.4
unnamed: COMMUNICATION.1, X3.6
unnamed: COMMUNICATION.2, X3.5
unnamed: COMMUNICATION.3, X3.4
unnamed: COMMUNICATION.4, X3.3
unnamed: COMMUNICATION.5, X3.2
unnamed: COMMUNICATION.6, X3.1
unnamed: COMMUNICATION.7, X2.1
unnamed: COMMUNICATION.8, X2.2
unnamed: PWML.8, X4.2
unnamed: PWML.7, X4.1
unnamed: PWMH.2, X5.2
unnamed: PWMH.1, X5.1
unnamed: ADCL.1, X6.8
unnamed: ADCH.1, X7.8
unnamed: ADCH.2, X7.7
unnamed: ADCL.2, X6.7
unnamed: ADCL.3, X6.6
unnamed: ADCL.4, X6.5
unnamed: ADCL.5, X6.4
unnamed: ADCL.6, X6.3
unnamed: ADCL.7, X6.2
unnamed: ADCL.8, X6.1
unnamed: ADCH.3, X7.6
unnamed: ADCH.4, X7.5
unnamed: ADCH.5, X7.4
unnamed: ADCH.6, X7.3
unnamed: ADCH.7, X7.2
unnamed: ADCH.8, X7.1
unnamed: X10.8, XIOH.1
unnamed: X11.1, XIOH.2
unnamed: X10.7, XIOH.3
unnamed: X10.6, XIOH.5
unnamed: X10.5, XIOH.7
unnamed: X10.4, XIOH.9
unnamed: X10.3, XIOH.11
unnamed: X10.2, XIOH.13
unnamed: X10.1, XIOH.15
unnamed: X11.2, XIOH.4
unnamed: X11.3, XIOH.6
unnamed: X11.4, XIOH.8
unnamed: X11.5, XIOH.10
unnamed: X11.6, XIOH.12
unnamed: X11.7, XIOH.14
unnamed: X11.8, XIOH.16
unnamed: X9.5, XIOL.7
unnamed: X9.4, XIOL.9
unnamed: X9.3, XIOL.11
unnamed: X9.2, XIOL.13
unnamed: X9.1, XIOL.15
unnamed: X8.4, XIOL.8
unnamed: X8.5, XIOL.10
unnamed: X8.6, XIOL.12
unnamed: X8.7, XIOL.14
unnamed: X8.8, XIOL.16
unnamed: POWER.1, X15.3
unnamed: POWER.4, X15.2
unnamed: C1.2, JP5.7, POWER.5, X15.1
unnamed: JP3.1, JP4.1, X12.1, X12.2
RESET: POWER.6, S1.1, S1.2
SCK: JP5.4, X9.8, XIOL.1

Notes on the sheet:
(SCK)
(MISO)
(MOSI)
(TX0)
(RX0)
(SS)
Arduino Mega 2560 Reference Design

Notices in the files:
parts and their libraries:
SparkFun-Aesthetics: Licensing: Creative Commons ShareAlike 4.0 International - https://creativecommons.org/licenses/by-sa/4.0
